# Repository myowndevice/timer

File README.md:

## Кухонный таймер

Кухонный таймер. Несложный прибор для учёта времени. 

Вы можете самостоятельно сделать этот современный прибор из данного набора деталей. Данный радиоконструктор базируется на микроконтроллере STM8 и позволит вам приобрести навыки программирования микроконтроллеров. Он имеет отличные, современные характеристики:

- Прямой и обратный отсчет времени до 999 минут
- Режим Игры — лото, игральная кость, бомба
- Учет рабочего времени с паузами и подтверждением
- Три предустановленных значения таймера
- Компактный размер
- Питание от аккумулятора, длительная работа от одного заряда
- Зарядка от micro usb
- Индикатор на 3 разряда
- Низкая стоимость
- Громкий сигнал различной тональности
- Широкий набор функций — Таймер, Секундомер, Игры: игральная кость, лото, бомба, возможность программирования.
- Компактный размер

Данный репозитарий содержит все необходимые файлы для изготовления кухонного таймера.Если вы будете скачивать файлы через web не забудьте скачать общую папку Kicadlib.

Ознакомится со схемой и подробным описанием кухонного таймера, программы, и порядка сборки можно, [прочитав эту подробную статью](http://myowndevice.ru/index.php/pribory/item/33-kukhonnyj-timer)

Также [здесь](http://myowndevice.ru) вы найдете подробное описание как сделать другие приборы, много теории о том, как их делать, методику изготовления печатных плат и много другого.

Изучай микроконтроллеры, делай платы дома, разрабатывай электронику сам!

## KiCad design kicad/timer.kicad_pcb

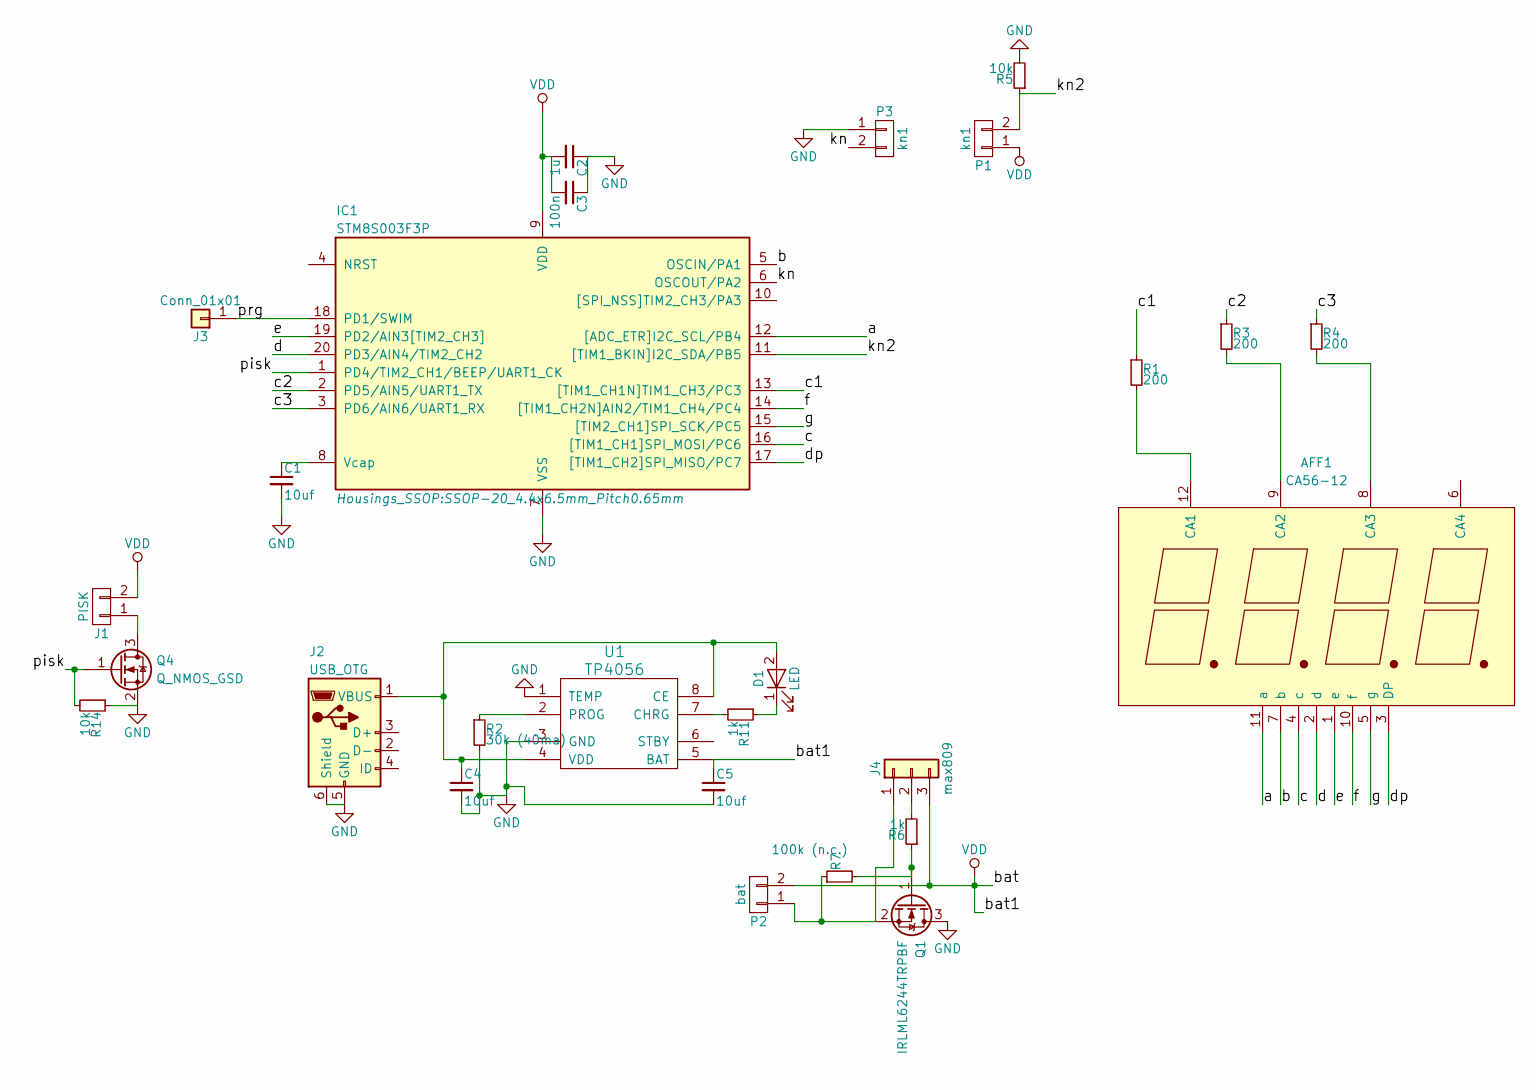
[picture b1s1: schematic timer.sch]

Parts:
AFF1: CA56-12; indicator_3cif
C1, C4, C5: 10uf; C_0805_HandSoldering
C2: 1u; C_0805_HandSoldering
C3: 100n; C_0603_HandSoldering
D1: LED; LED_0603_HandSoldering
IC1: STM8S003F3P; SSOP-20_4.4x6.5mm_Pitch0.65mm
J1: PISK; hc0903a
J2: USB_OTG; usb5s
J3: Conn_01x01; 1pin_sq
J4: max809; SOT-23
P1: kn1; SW_Tactile_SKHH_Angled
P2: bat; Pin_Header_Angled_1x02_Pitch2.54mm
P3: kn1; SW_PUSH_6mm_h8mm
Q1: IRLML6244TRPBF; SOT-23
Q4: Q_NMOS_GSD; SOT-23
R1, R3, R4: 200; R_0603_HandSoldering
R2: 30k (40ma); R_0603_HandSoldering
R5, R14: 10k; R_0603_HandSoldering
R6, R11: 1k; R_0603_HandSoldering
R7: 100k (n.c.); R_0603_HandSoldering
U1: TP4056; SOIC-8-1EP_3.9x4.9mm_Pitch1.27mm

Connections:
/a: AFF1.11 (a), IC1.12 ([ADC_ETR]I2C_SCL/PB4)
/b: AFF1.7 (b), IC1.5 (OSCIN/PA1)
/c: AFF1.4 (c), IC1.16 ([TIM1_CH1]SPI_MOSI/PC6)
/c1: IC1.13 ([TIM1_CH1N]TIM1_CH3/PC3), R1.1
/c2: IC1.2 (PD5/AIN5/UART1_TX), R3.1
/c3: IC1.3 (PD6/AIN6/UART1_RX), R4.1
/d: AFF1.2 (d), IC1.20 (PD3/AIN4/TIM2_CH2)
/dp: AFF1.3 (DP), IC1.17 ([TIM1_CH2]SPI_MISO/PC7)
/e: AFF1.1 (e), IC1.19 (PD2/AIN3[TIM2_CH3])
/f: AFF1.10 (f), IC1.14 ([TIM1_CH2N]AIN2/TIM1_CH4/PC4)
/g: AFF1.5 (g), IC1.15 ([TIM2_CH1]SPI_SCK/PC5)
/kn: IC1.6 (OSCOUT/PA2), P3.2
/kn2: IC1.11 ([TIM1_BKIN]I2C_SDA/PB5), P1.2, R5.1
/pisk: IC1.1 (PD4/TIM2_CH1/BEEP/UART1_CK), Q4.1 (G), R14.2
/prg: IC1.18 (PD1/SWIM), J3.1
GND: C1.2, C2.1, C3.1, C4.2, C5.2, IC1.7 (VSS), J2.5 (GND), J2.6 (Shield), P3.1, Q1.3 (D), Q4.2 (S), R2.2, R5.2, R14.1, U1.1 (TEMP), U1.3 (GND), U1.9 (GND)
unnamed: AFF1.8 (CA3), R4.2
unnamed: AFF1.9 (CA2), R3.2
unnamed: AFF1.12 (CA1), R1.2
unnamed: C1.1, IC1.8 (Vcap)
unnamed: C4.1, D1.2 (A), J2.1 (VBUS), U1.4 (VDD), U1.8 (CE)
unnamed: D1.1 (K), R11.1
unnamed: J1.1, Q4.3 (D)
unnamed: J4.1, P2.1, Q1.2 (S), R7.1
unnamed: J4.2, R6.2
unnamed: Q1.1 (G), R6.1, R7.2
unnamed: R2.1, U1.2 (PROG)
unnamed: R11.2, U1.7 (CHRG)
VDD: C2.2, C3.2, C5.1, IC1.9 (VDD), J1.2, J4.3, P1.1, P2.2, U1.5 (BAT)

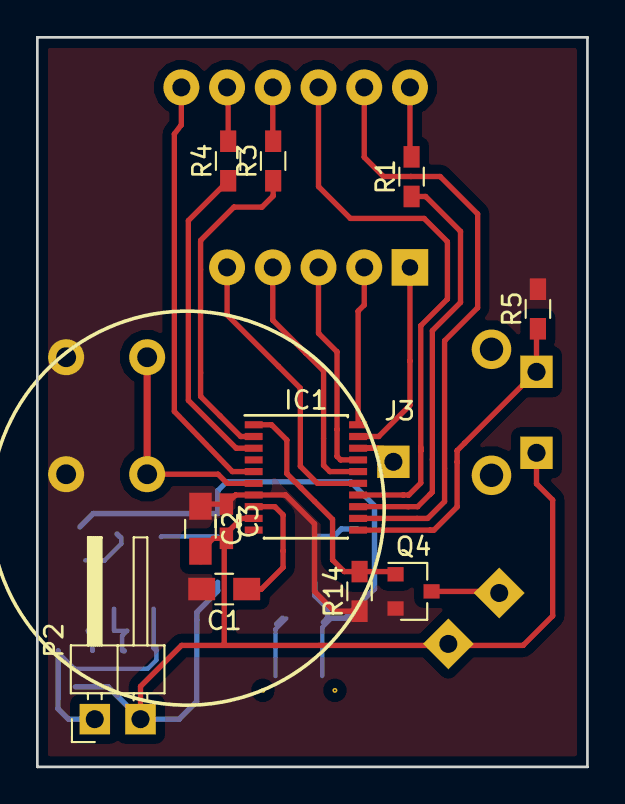
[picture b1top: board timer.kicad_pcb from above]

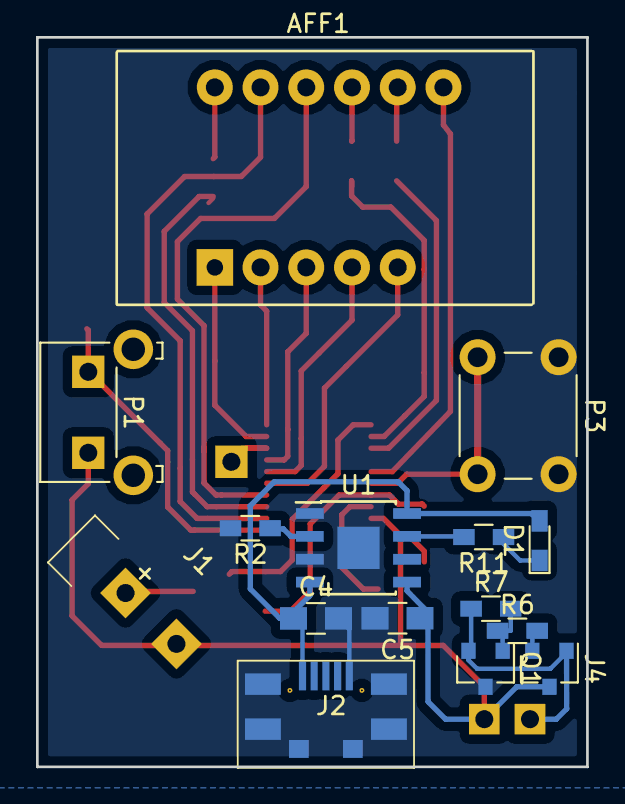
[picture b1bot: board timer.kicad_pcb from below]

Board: 2 copper layers, 30.6 x 40.5 mm, 27 parts (15 on the bottom side), 29 nets.

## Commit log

2017-11-07 start
